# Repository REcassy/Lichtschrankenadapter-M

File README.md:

# Lichtschrankenadapter-M
Open sensor for use with any standard light barrier on a Mobile Cassy.

This repo is under active development, so schematic and pcb files may not match always. Use the current release for production: https://github.com/REcassy/Lichtschranke-M/releases/tag/v1.0

## Compatible barriers
The Mobile Cassy pulls J2 to 5V (barrier 1) and J3 to 3.7V (barrier 2). Your light barrier needs to pull that down to less than 2V to register an event. A photo-transistor is optimal for that. You barrier can make use of +5V / GND jacks to power the light source. You should try to use as little current as possible to not put a strain on the Mobile Cassy's batteries, but anything up to 100mA seems to be acceptable.

Use at your own risk - especially drawing power. There is no public information on current limiting or fuses inside the Mobile Cassy. Always prefer LED to incandescent bulbs.

## Testing
For testing I included an Arduino simulator code. For this you need to connect the I<sup>2</sup>C pins of your Arduino (e.g. on a Uno Pins the upper right ones) to the I<sup>2</sup>C pins of the Cassy Mini-DIN interface (SDA: 1 and SCK: 5) as well as pin 7 of the Arduino (change this, if this is no digital out on your Arduino) to Mini-DIN pin 2.

## Programming your ATtiny25
The included ino file is intended for use with the Arduino IDE and any Arduino as an ISP Programmer. You need to:
* load the ISP sketch from the Arduino IDE (File->Examples->11. ArduinoISP) onto your Arduino Uno
* install ATTinyCore (https://github.com/SpenceKonde/ATTinyCore) as a board manager into your Arduino IDE 
* connect the Arduino to the ATTiny according to this graphic:

* when using other ATTiny chips check the datasheet or the ATtinyCore [repo][attiny-boards]
* set Tools->Board to ATtinyCore-> "ATtiny25/45/85 (no bootloader)"
* set Tools->Chip to ATtiny25
* set Tools->Programmer to "Arduino as ISP"
* use Tools->Burn Bootloader to set the appropriate E-Fuses in your ATtiny (only necessary with a brand new ATtiny)
* use Sketch->Upload Using Programmer

There are of course countless other ways to program your ATtiny. You can find the .hex file in the ATtiny directory.

## Schematic and PCB
The schematic and PCB files were created with KiCAD.

Be aware that earlier photos on my blog show a switched J4/J5 label (GND and 5V) as well as an incorrectly polarized C2.

The PCB file ending in "-tube" is used with brass tubes (see BOM) as connectors the one ending in "-jack" with ready made 4mm jacks.

Below you can see both boards fully populated:

## BOM
You need the following (given in brackets are Reichelt ordering numbers for reference):

| Part Label  | Description | Form factor | Reichelt number |
| ------------- | ------------- | ------------- | ------------- |
| U1  |  ATiny25 | DIP-8 | ATTINY 25-20 PU |
| U2 | USBLC6 | SOT-23-6 |  USBLC6-2SC6 |
| C1, C3 | 50V 100nF ceramic cap | 1206 |  WAL 1206B104K500 |
| C2 | 50V 10µF electrolytic cap | RM2,5 |  SU-A 10U 50|
| R1, R2 | 0,25W 5K1 resistor | 0207 |  1/4W 5,1K |
| J1 | Mini-Din 6 connector | N/A | EB-DIOS M06 |
| J2-J5 | 4mm ID, 5mm OD brass tube | N/A | N/A |
| J2-J5 | 4mm laboratory jacks | N/A | SEP 2610 F48  |

choose either J2-J5 option and the appropriate PCB design.

## Gerber and drill files
The gerber and drill files were exported from KiCAD and are ready to be sent to any PCB manufacturer of your choice. The PCB design features no vias. Any standard double sided process will suffice.
Please choose the correct set of files for your desired jacks.

Below are the renderings for both variants:

## 3D-printed case
A 3D printable case is currently in development.

[attiny-boards]: https://github.com/SpenceKonde/ATTinyCore/blob/v2.0.0-devThis-is-the-head-submit-PRs-against-this/avr/extras/ATtiny_x5.md

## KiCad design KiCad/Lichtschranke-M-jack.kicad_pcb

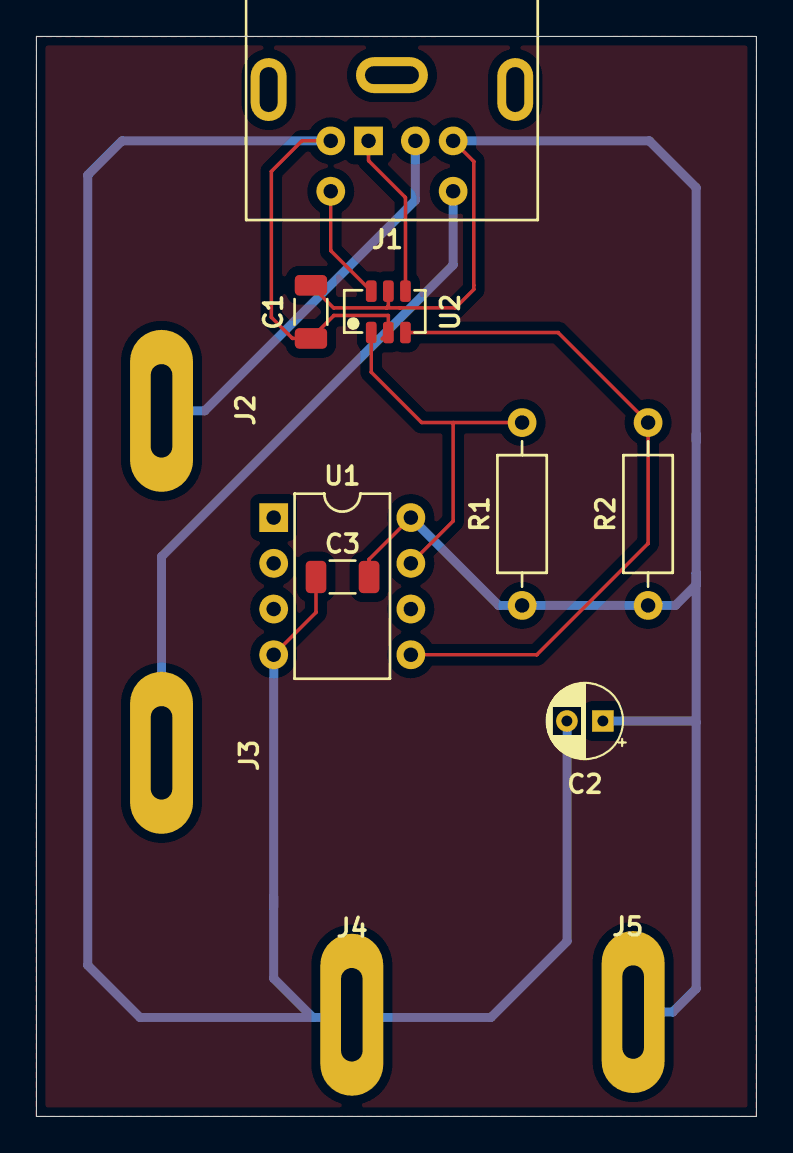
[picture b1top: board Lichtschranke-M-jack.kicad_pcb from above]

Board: 2 copper layers, 40.0 x 60.0 mm, 12 parts (0 on the bottom side), 8 nets.

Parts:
C1, C3: C; C_1206_3216Metric
C2: C_Polarized; CP_Radial_D4.0mm_P2.00mm
J1: Mini-DIN-6; Connector_Mini-DIN_Female_6Pin_2rows
J2, J3, J4, J5: Conn_01x01_Socket; Banana-Slot
R1, R2: R; R_Axial_DIN0207_L6.3mm_D2.5mm_P10.16mm_Horizontal
U1: ATtiny25-20P; DIP-8_W7.62mm
U2: USBLC6

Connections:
+5V: C1.1, C2.1, C3.2, J1.4, J5.1, R1.1, R2.1, U1.8 (VCC), U2.5 (VBus)
E: J1.2, J2.1
F: J1.6, J3.1
GND: C1.2, C2.2, C3.1, J1.3, J4.1, U1.4 (GND), U2.2 (GND)
unnamed: R2.2, U1.5 (AREF/PB0), U2.3 (I/O2)
unnamed: R1.2, U1.7 (PB2), U2.1 (I/O1)
SCK: J1.5, U2.6 (I/O1)
SDA: J1.1, U2.4 (I/O2)

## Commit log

2024-09-08 Rename Lichtschranke-M.kicad_pcb to Lichtschranke-M-tube.kicad_pcb
2024-09-08 Create Lichtschranke-M-NPTH
2024-09-08 Create placeholder
2024-09-08 Create LICENSE
2024-09-09 Update README.md
    Extended programming instructions

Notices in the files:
KiCad/Lichtschranke-M-jack.kicad_pcb:
recassy.github.io (c) 2024
